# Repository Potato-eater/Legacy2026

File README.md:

# Legacy2026
github repo for Robocup Junior Australia lightweight soccer team

poster for state competition: https://canva.link/pb0ula68jbszzvj

All programs are annotated within their own files.

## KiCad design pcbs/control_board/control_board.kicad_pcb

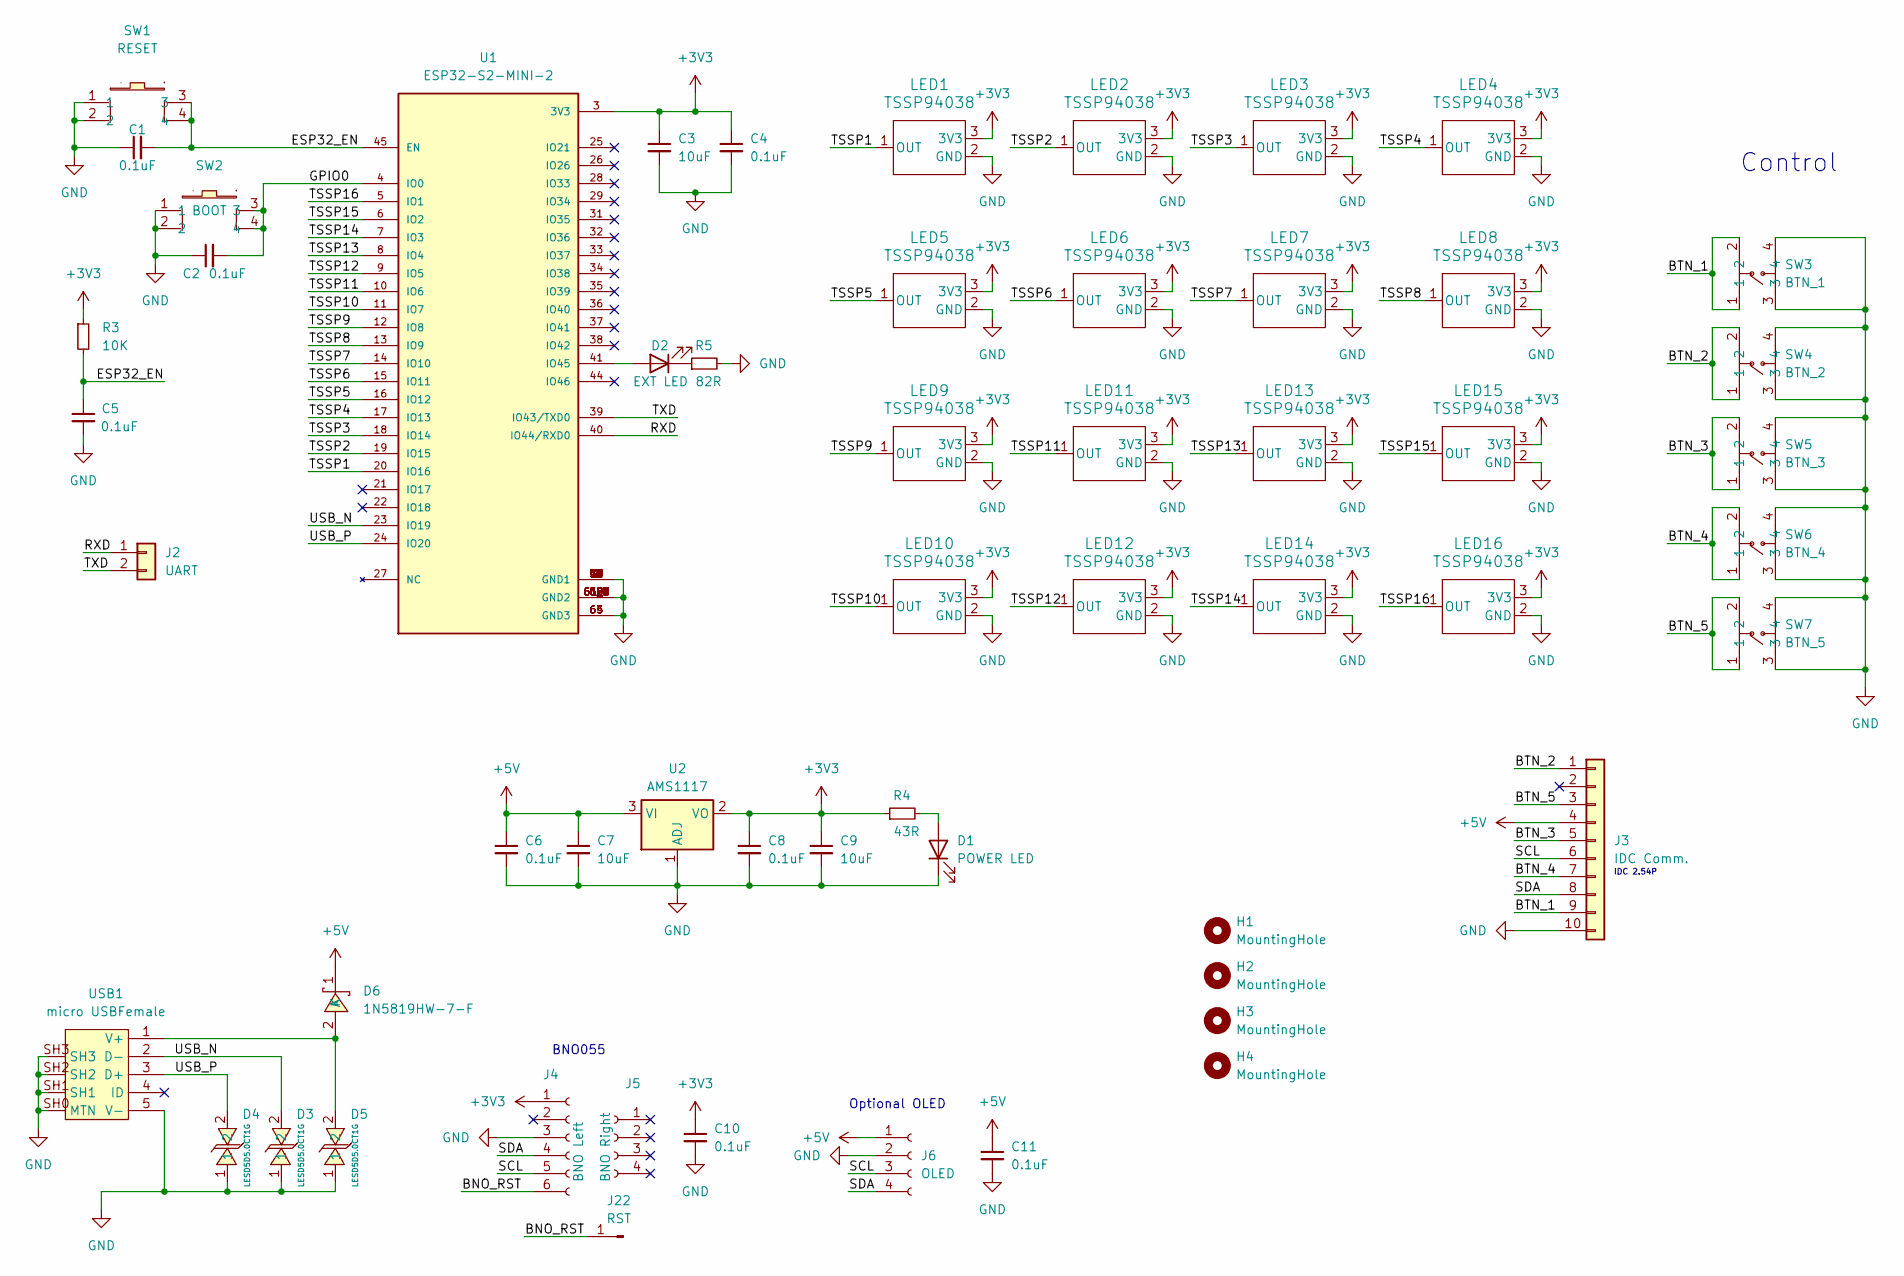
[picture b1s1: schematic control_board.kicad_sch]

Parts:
C1, C2, C4, C5, C6, C8, C10, C11: 0.1uF; C_0402_1005Metric
C3, C7, C9: 10uF; C_0603_1608Metric
D1: POWER LED; LED_0603_1608Metric
D2: EXT LED; LED_0603_1608Metric
D3, D4, D5: LESD5D5.0CT1G; SOD-523_L1.2-W0.8-LS1.6-BI; LCSC Part C5274290
D6: 1N5819HW-7-F; SOD-123_L2.7-W1.6-LS3.7-RD; LCSC Part C82544
H1, H2, H3, H4: MountingHole; MountingHole_3.5mm
J2: UART; JST_XH_B2B-XH-A_1x02_P2.50mm_Vertical
J3: IDC Comm.; IDC-Header_2x05_P2.54mm_Vertical
J4: BNO Left; PinSocket_1x06_P2.54mm_Vertical
J5: BNO Right; PinSocket_1x04_P2.54mm_Vertical
J6: OLED; PinSocket_1x04_P2.54mm_Vertical
J22: RST; PinHeader_1x01_P2.54mm_Vertical
LED1, LED2, LED3, LED4, LED5, LED6, LED7, LED8, LED9, LED10, LED11, LED12, LED13, LED14, LED15, LED16: TSSP94038
R3: 10K; R_0603_1608Metric
R4: 43R; R_0603_1608Metric
R5: 82R; R_0603_1608Metric
SW1: RESET; SW-SMD_4P_PTS810SJM250SMTRLFS; LCSC Part C221897
SW2: BOOT; SW-SMD_4P_PTS810SJM250SMTRLFS; LCSC Part C221897
SW3: BTN_1; SW-TH_4P-L6.0-W6.0-P4.50-LS6.3; LCSC Part C2889001
SW4: BTN_2; SW-TH_4P-L6.0-W6.0-P4.50-LS6.3; LCSC Part C2889001
SW5: BTN_3; SW-TH_4P-L6.0-W6.0-P4.50-LS6.3; LCSC Part C2889001
SW6: BTN_4; SW-TH_4P-L6.0-W6.0-P4.50-LS6.3; LCSC Part C2889001
SW7: BTN_5; SW-TH_4P-L6.0-W6.0-P4.50-LS6.3; LCSC Part C2889001
U1: ESP32-S2-MINI-2; PARTREV v0.5
U2: AMS1117; SOT-223-3_TabPin2
USB1: micro USBFemale; MICRO-USB-SMD_5P-P0.65-H-F_C10418; LCSC Part C10418

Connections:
+3V3: C3.1, C4.1, C8.1, C9.1, C10.1, J4.1, LED1.3 (3V3), LED2.3 (3V3), LED3.3 (3V3), LED4.3 (3V3), LED5.3 (3V3), LED6.3 (3V3), LED7.3 (3V3), LED8.3 (3V3), LED9.3 (3V3), LED10.3 (3V3), LED11.3 (3V3), LED12.3 (3V3), LED13.3 (3V3), LED14.3 (3V3), LED15.3 (3V3), LED16.3 (3V3), R3.1, R4.1, U1.3 (3V3), U2.2 (VO)
+5V: C6.1, C7.1, C11.1, D6.1 (K), J3.4, J6.1, U2.3 (VI)
/BNO_RST: J4.6, J22.1
/BTN_1: J3.9, SW3.1, SW3.2
/BTN_2: J3.1, SW4.1, SW4.2
/BTN_3: J3.5, SW5.1, SW5.2
/BTN_4: J3.7, SW6.1, SW6.2
/BTN_5: J3.3, SW7.1, SW7.2
/ESP32_EN: C1.2, C5.1, R3.2, SW1.3, SW1.4, U1.45 (EN)
/GPIO0: C2.2, SW2.3, SW2.4, U1.4 (IO0)
/RXD: J2.1, U1.40 (IO44/RXD0)
/SCL: J3.6, J4.5, J6.3
/SDA: J3.8, J4.4, J6.4
/TSSP1: LED1.1 (OUT), U1.20 (IO16)
/TSSP2: LED2.1 (OUT), U1.19 (IO15)
/TSSP3: LED3.1 (OUT), U1.18 (IO14)
/TSSP4: LED4.1 (OUT), U1.17 (IO13)
/TSSP5: LED5.1 (OUT), U1.16 (IO12)
/TSSP6: LED6.1 (OUT), U1.15 (IO11)
/TSSP7: LED7.1 (OUT), U1.14 (IO10)
/TSSP8: LED8.1 (OUT), U1.13 (IO9)
/TSSP9: LED9.1 (OUT), U1.12 (IO8)
/TSSP10: LED10.1 (OUT), U1.11 (IO7)
/TSSP11: LED11.1 (OUT), U1.10 (IO6)
/TSSP12: LED12.1 (OUT), U1.9 (IO5)
/TSSP13: LED13.1 (OUT), U1.8 (IO4)
/TSSP14: LED14.1 (OUT), U1.7 (IO3)
/TSSP15: LED15.1 (OUT), U1.6 (IO2)
/TSSP16: LED16.1 (OUT), U1.5 (IO1)
/TXD: J2.2, U1.39 (IO43/TXD0)
/USB_N: D3.2, U1.23 (IO19), USB1.2 (D-)
/USB_P: D4.2, U1.24 (IO20), USB1.3 (D+)
GND: C1.1, C2.1, C3.2, C4.2, C5.2, C6.2, C7.2, C8.2, C9.2, C10.2, C11.2, D1.1 (K), D3.1, D4.1, D5.1, J3.10, J4.3, J6.2, LED1.2 (GND), LED2.2 (GND), LED3.2 (GND), LED4.2 (GND), LED5.2 (GND), LED6.2 (GND), LED7.2 (GND), LED8.2 (GND), LED9.2 (GND), LED10.2 (GND), LED11.2 (GND), LED12.2 (GND), LED13.2 (GND), LED14.2 (GND), LED15.2 (GND), LED16.2 (GND), R5.2, SW1.1, SW1.2, SW2.1, SW2.2, SW3.3, SW3.4, SW4.3, SW4.4, SW5.3, SW5.4, SW6.3, SW6.4, SW7.3, SW7.4, U1.1 (GND1), U1.2 (GND1), U1.30 (GND1), U1.42 (GND1), U1.43 (GND1), U1.46 (GND1), U1.47 (GND1), U1.48 (GND1), U1.49 (GND1), U1.50 (GND1), U1.51 (GND1), U1.52 (GND1), U1.53 (GND1), U1.54 (GND1), U1.55 (GND1), U1.56 (GND2), U1.57 (GND2), U1.58 (GND2), U1.59 (GND2), U1.60 (GND2), U1.61_1 (GND2), U1.61_2 (GND2), U1.61_3 (GND2), U1.61_4 (GND2), U1.61_5 (GND2), U1.61_6 (GND2), U1.61_7 (GND2), U1.61_8 (GND2), U1.61_9 (GND2), U1.62 (GND2), U1.63 (GND3), U1.64 (GND3), U1.65 (GND3), U2.1 (ADJ), USB1.5 (V-), USB1.SH0 (MTN), USB1.SH1, USB1.SH2, USB1.SH3
unnamed: D1.2 (A), R4.2
unnamed: D2.2 (A), U1.41 (IO45)
unnamed: D2.1 (K), R5.1
unnamed: D5.2, D6.2 (A), USB1.1 (V+)

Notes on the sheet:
Optional OLED
Control
BNO055
IDC 2.54P

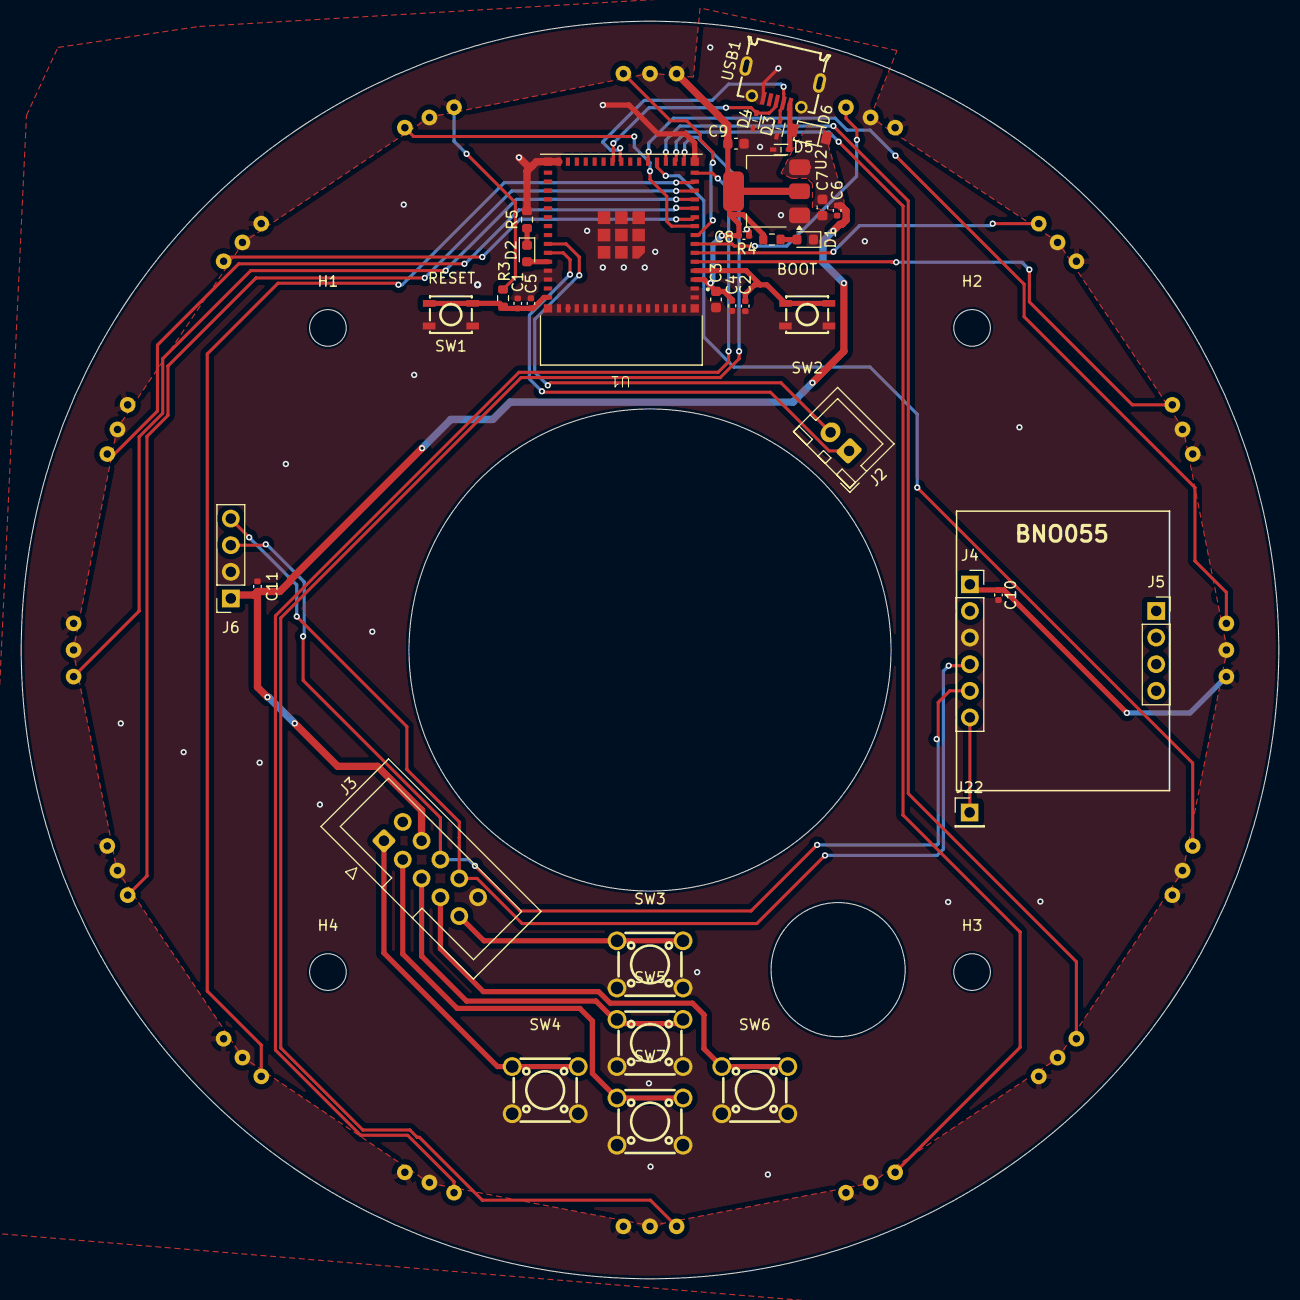
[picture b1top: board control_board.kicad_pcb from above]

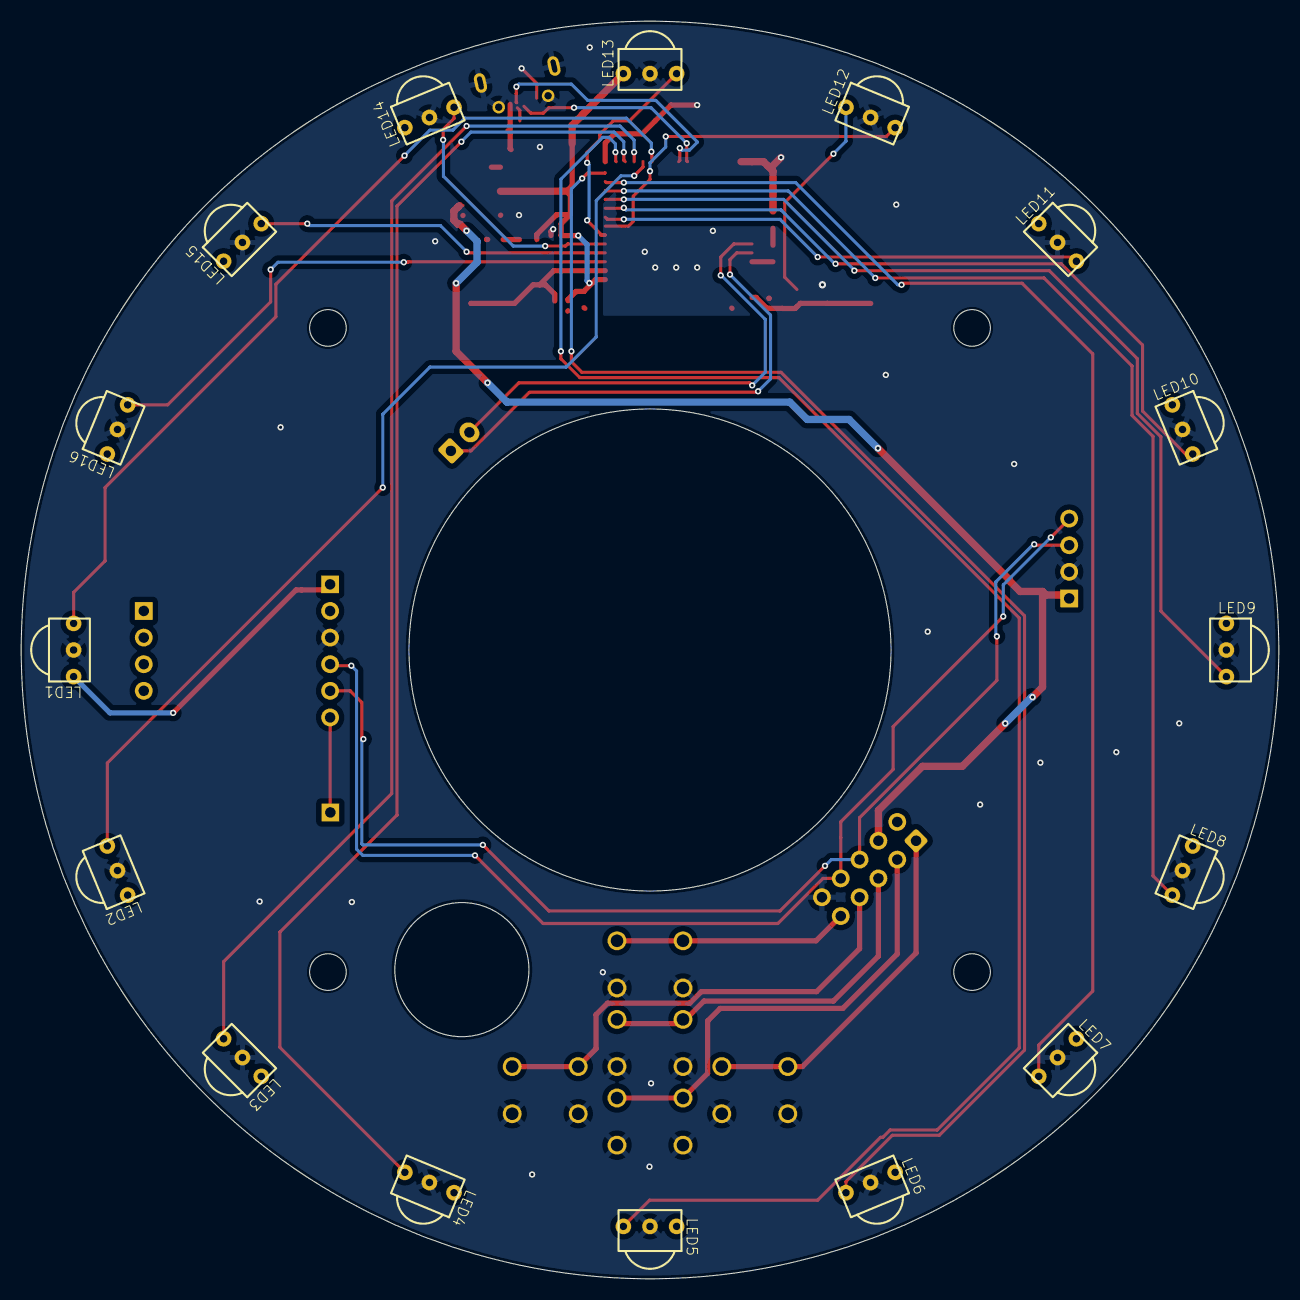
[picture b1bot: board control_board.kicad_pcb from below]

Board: 2 copper layers, 120.0 x 120.0 mm, 56 parts (16 on the bottom side), 37 nets.

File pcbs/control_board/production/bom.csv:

Designator,Footprint,Quantity,Value,LCSC Part #
"C1, C10, C11, C2, C4, C5, C6, C8",0402,8,0.1uF,
"C3, C7, C9",0603,3,10uF,
D1,0603,1,POWER LED,
D2,0603,1,EXT LED,
"D3, D4, D5",SOD-523_L1.2-W0.8-LS1.6-BI,3,LESD5D5.0CT1G,C5274290
D6,SOD-123_L2.7-W1.6-LS3.7-RD,1,1N5819HW-7-F,C82544
J2,JST_XH_B2B-XH-A_1x02_P2.50mm_Vertical,1,UART,
J22,PinHeader_1x01_P2.54mm_Vertical,1,RST,
J3,IDC-Header_2x05_P2.54mm_Vertical,1,IDC Comm.,
J4,PinSocket_1x06_P2.54mm_Vertical,1,BNO Left,
J5,PinSocket_1x04_P2.54mm_Vertical,1,BNO Right,
J6,PinSocket_1x04_P2.54mm_Vertical,1,OLED,
"LED1, LED10, LED11, LED12, LED13, LED14, LED15, LED16, LED2, LED3, LED4, LED5, LED6, LED7, LED8, LED9",TSSP94038,16,TSSP94038,
R3,0603,1,10K,
R4,0603,1,43R,
R5,0603,1,82R,
SW1,SW-SMD_4P_PTS810SJM250SMTRLFS,1,RESET,C221897
SW2,SW-SMD_4P_PTS810SJM250SMTRLFS,1,BOOT,C221897
SW3,SW-TH_4P-L6.0-W6.0-P4.50-LS6.3,1,BTN_1,C2889001
SW4,SW-TH_4P-L6.0-W6.0-P4.50-LS6.3,1,BTN_2,C2889001
SW5,SW-TH_4P-L6.0-W6.0-P4.50-LS6.3,1,BTN_3,C2889001
SW6,SW-TH_4P-L6.0-W6.0-P4.50-LS6.3,1,BTN_4,C2889001
SW7,SW-TH_4P-L6.0-W6.0-P4.50-LS6.3,1,BTN_5,C2889001
U1,ESP32-S2-MINI-2,1,ESP32-S2-MINI-2,
U2,SOT-223-3_TabPin2,1,AMS1117,
USB1,MICRO-USB-SMD_5P-P0.65-H-F_C10418,1,micro USBFemale,C10418

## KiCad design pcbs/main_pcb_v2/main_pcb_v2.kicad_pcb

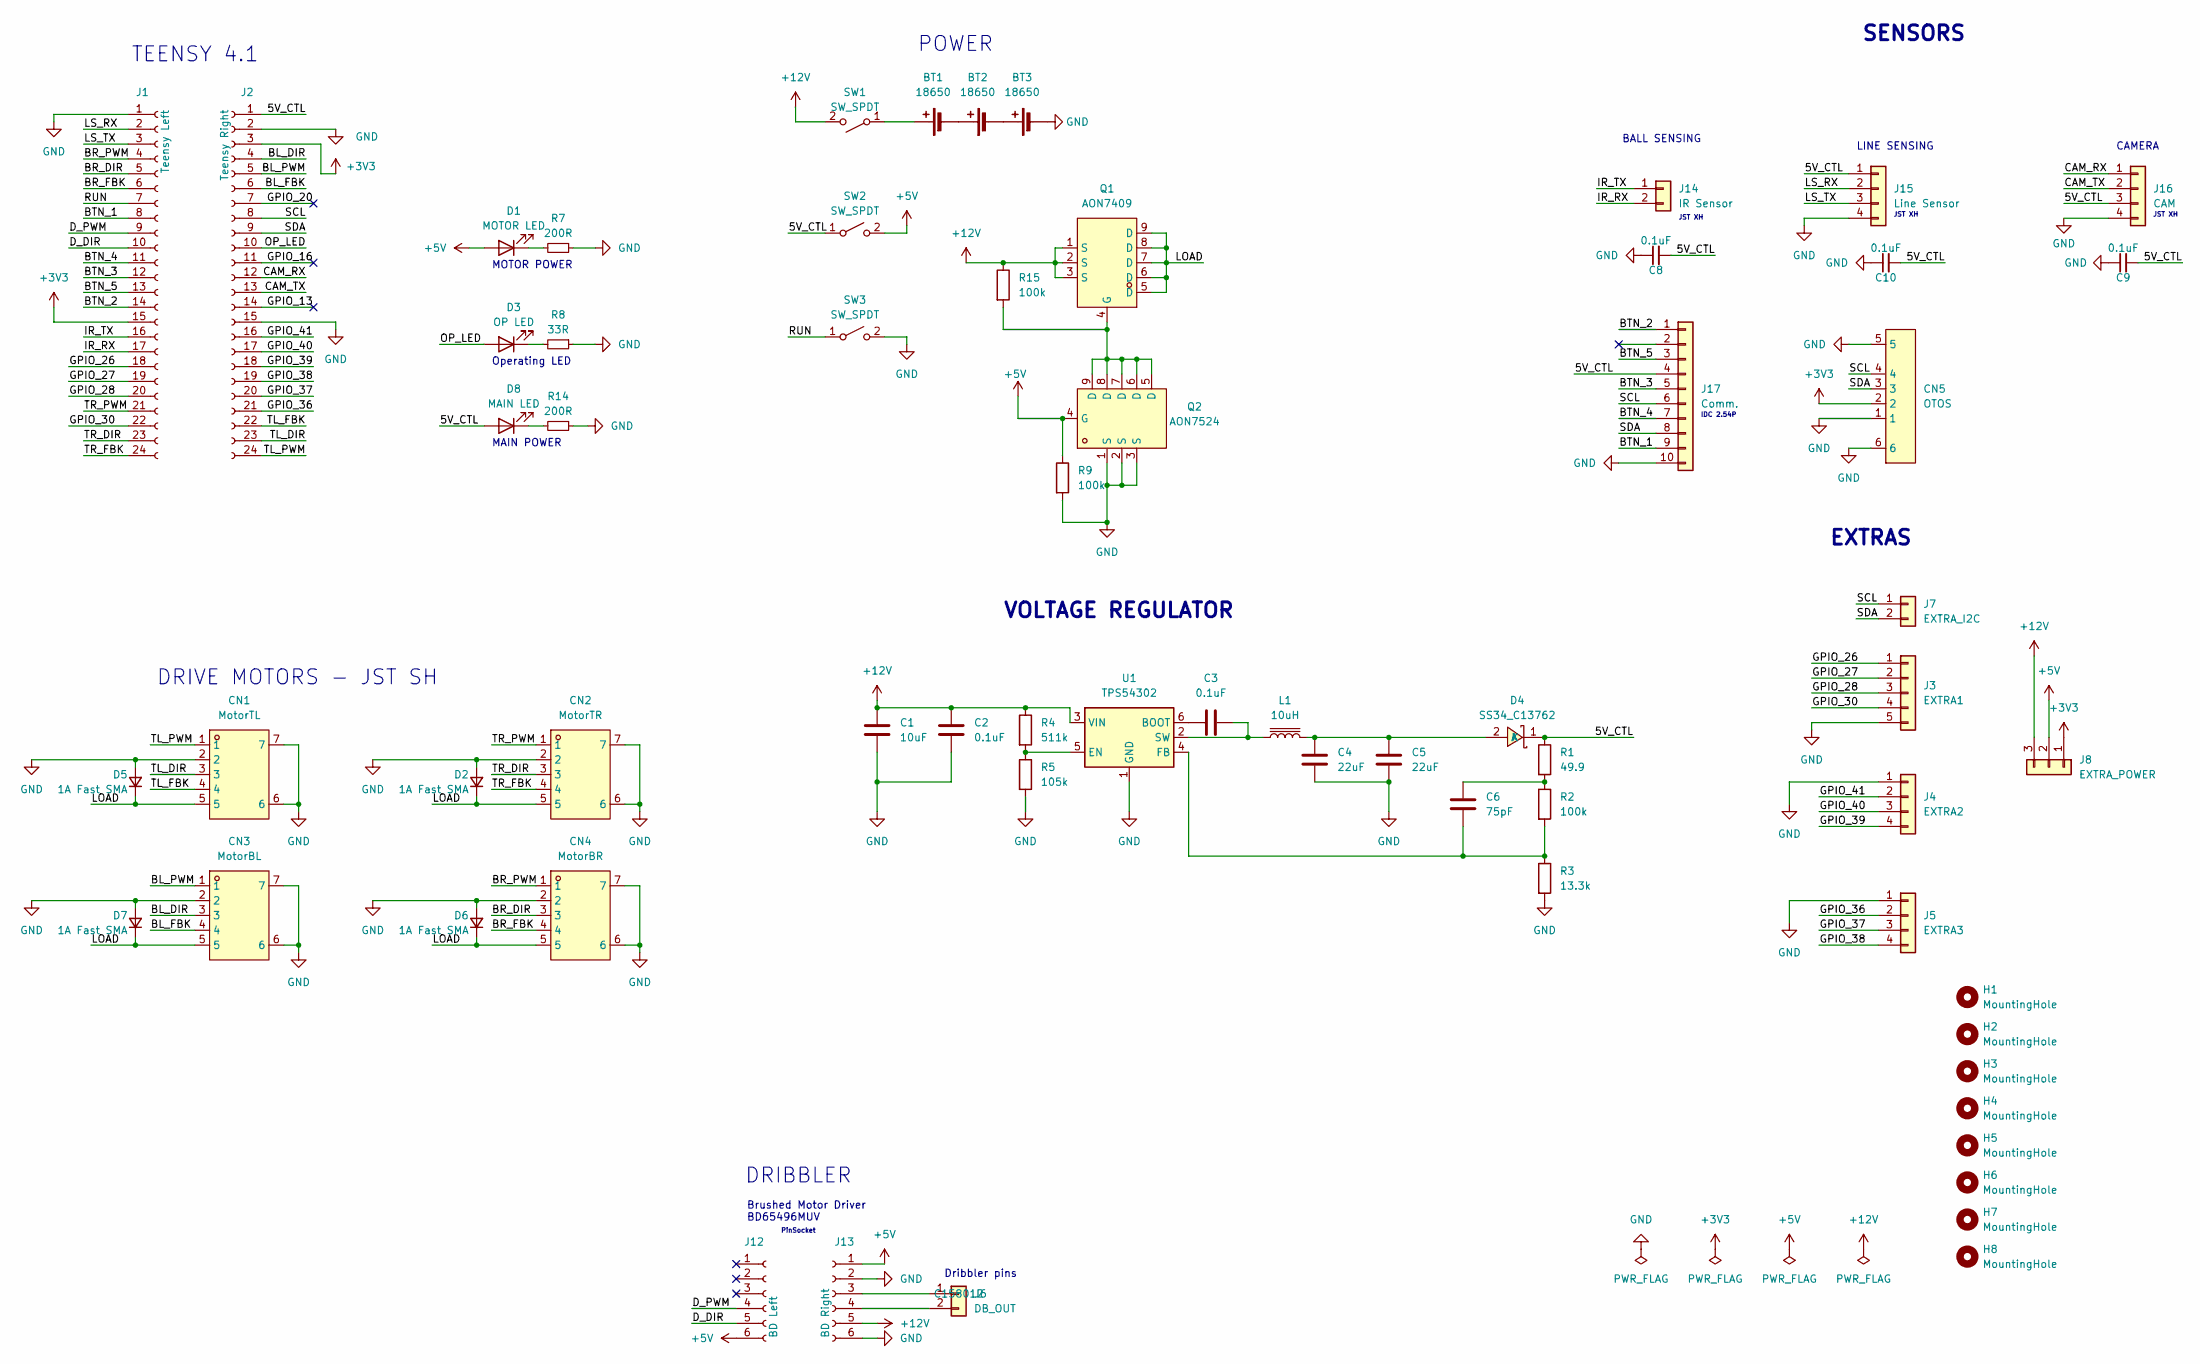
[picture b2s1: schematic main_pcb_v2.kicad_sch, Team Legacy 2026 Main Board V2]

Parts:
BT1, BT2, BT3: 18650; Altronics_S5037
C1: 10uF; C_0805_2012Metric
C2, C3, C8, C9: 0.1uF; C_0805_2012Metric
C4, C5: 22uF; C_0805_2012Metric
C6: 75pF; C_0805_2012Metric
C10: 0.1uF; C_0402_1005Metric
CN1: MotorTL; CONN-SMD_SM05B-SRSS-TB-LF-SN; LCSC Part C136657
CN2: MotorTR; CONN-SMD_SM05B-SRSS-TB-LF-SN; LCSC Part C136657
CN3: MotorBL; CONN-SMD_SM05B-SRSS-TB-LF-SN; LCSC Part C136657
CN4: MotorBR; CONN-SMD_SM05B-SRSS-TB-LF-SN; LCSC Part C136657
CN5: OTOS; CONN-SMD_4P-P1.00_SM04B-SRSS-TB-LF-SN; LCSC Part C160404
D1: MOTOR LED; LED_0603_1608Metric
D2, D5, D6, D7: 1A Fast SMA; D_SMA
D3: OP LED; LED_0805_2012Metric
D4: SS34_C13762; SMB_L4.6-W3.6-LS5.3-RD; LCSC Part C13762
D8: MAIN LED; LED_0603_1608Metric
H1, H2, H3, H4, H5, H6, H7, H8: MountingHole; MountingHole_3.5mm
J1: Teensy Left; PinSocket_1x24_P2.54mm_Vertical
J2: Teensy Right; PinSocket_1x24_P2.54mm_Vertical
J3: EXTRA1; PinSocket_1x05_P2.54mm_Vertical
J4: EXTRA2; PinSocket_1x04_P2.54mm_Vertical
J5: EXTRA3; PinSocket_1x04_P2.54mm_Vertical
J6: DB_OUT; JST_XH_B2B-XH-A_1x02_P2.50mm_Vertical
J7: EXTRA_I2C; JST_XH_B2B-XH-A_1x02_P2.50mm_Vertical
J8: EXTRA_POWER; PinSocket_1x03_P2.54mm_Vertical
J12: BD Left; PinSocket_1x06_P2.54mm_Vertical
J13: BD Right; PinSocket_1x06_P2.54mm_Vertical
J14: IR Sensor; JST_XH_B2B-XH-A_1x02_P2.50mm_Vertical
J15: Line Sensor; JST_XH_B4B-XH-A_1x04_P2.50mm_Vertical
J16: CAM; JST_XH_B4B-XH-A_1x04_P2.50mm_Vertical
J17: Comm.; IDC-Header_2x05_P2.54mm_Vertical
L1: 10uH; IND-SMD_L11.0-W10.0
Q1: AON7409; WDFN-8_L3.0-W3.0-P0.65-LS3.3-BL-EP; MPN AON7409; LCSC Part C41348138
Q2: AON7524; DFN-8_L3.0-W3.0-P0.65-BL; LCSC Part C431195
R1: 49.9; R_0603_1608Metric
R2, R9, R15: 100k; R_0603_1608Metric
R3: 13.3k; R_0603_1608Metric
R4: 511k; R_0603_1608Metric
R5: 105k; R_0603_1608Metric
R7, R14: 200R; R_0603_1608Metric
R8: 33R; R_0603_1608Metric
SW1, SW2, SW3: SW_SPDT; CONN-TH_2P-P5.00_WJ128V-5.0-2P
U1: TPS54302; SOT-23-6

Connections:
+3V3: CN5.2, J1.15, J2.3, J8.1
+5V: D1.2 (A), J8.2, J12.6, J13.1, Q2.4 (G), R9.1, SW2.2 (B)
+12V: C1.1, C2.1, J8.3, J13.5, Q1.1 (S), Q1.2 (S), Q1.3 (S), R4.1, R15.1, SW1.2 (B), U1.3 (VIN)
/5V_CTL: C8.2, C9.2, C10.2, D4.1 (K), D8.2 (A), J2.1, J15.1, J16.3, J17.4, R1.1, SW2.1 (A)
/BL_DIR: CN3.3, J2.4
/BL_FBK: CN3.4, J2.6
/BL_PWM: CN3.1, J2.5
/BR_DIR: CN4.3, J1.5
/BR_FBK: CN4.4, J1.6
/BR_PWM: CN4.1, J1.4
/BTN_1: J1.8, J17.9
/BTN_2: J1.14, J17.1
/BTN_3: J1.12, J17.5
/BTN_4: J1.11, J17.7
/BTN_5: J1.13, J17.3
/CAM_RX: J2.12, J16.1
/CAM_TX: J2.13, J16.2
/D_DIR: J1.10, J12.5
/D_PWM: J1.9, J12.4
/GPIO_13: J2.14
/GPIO_16: J2.11
/GPIO_20: J2.7
/GPIO_26: J1.18, J3.1
/GPIO_27: J1.19, J3.2
/GPIO_28: J1.20, J3.3
/GPIO_30: J1.22, J3.4
/GPIO_36: J2.21, J5.2
/GPIO_37: J2.20, J5.3
/GPIO_38: J2.19, J5.4
/GPIO_39: J2.18, J4.4
/GPIO_40: J2.17, J4.3
/GPIO_41: J2.16, J4.2
/IR_RX: J1.17, J14.2
/IR_TX: J1.16, J14.1
/LOAD: CN1.5, CN2.5, CN3.5, CN4.5, D2.1 (K), D5.1 (K), D6.1 (K), D7.1 (K), Q1.5 (D), Q1.6 (D), Q1.7 (D), Q1.8 (D), Q1.9 (D)
/LS_RX: J1.2, J15.2
/LS_TX: J1.3, J15.3
/OP_LED: D3.2 (A), J2.10
/RUN: J1.7, SW3.1 (A)
/SCL: CN5.4, J2.8, J7.1, J17.6
/SDA: CN5.3, J2.9, J7.2, J17.8
/TL_DIR: CN1.3, J2.23
/TL_FBK: CN1.4, J2.22
/TL_PWM: CN1.1, J2.24
/TR_DIR: CN2.3, J1.23
/TR_FBK: CN2.4, J1.24
/TR_PWM: CN2.1, J1.21
GND: BT3.2 (-), C1.2, C2.2, C4.1, C5.1, C8.1, C9.1, C10.1, CN1.2, CN1.6, CN1.7, CN2.2, CN2.6, CN2.7, CN3.2, CN3.6, CN3.7, CN4.2, CN4.6, CN4.7, CN5.1, CN5.5, CN5.6, D2.2 (A), D5.2 (A), D6.2 (A), D7.2 (A), J1.1, J2.2, J2.15, J3.5, J4.1, J5.1, J13.2, J13.6, J15.4, J16.4, J17.10, Q2.1 (S), Q2.2 (S), Q2.3 (S), R3.2, R5.2, R7.1, R8.1, R9.2, R14.1, SW3.2 (B), U1.1 (GND)
unnamed: BT1.1 (+), SW1.1 (A)
unnamed: BT1.2 (-), BT2.1 (+)
unnamed: BT2.2 (-), BT3.1 (+)
unnamed: C6.2, R1.2, R2.1
unnamed: D1.1 (K), R7.2
unnamed: D3.1 (K), R8.2
unnamed: C4.2, C5.2, D4.2 (A), L1.2
unnamed: D8.1 (K), R14.2
unnamed: J6.1, J13.3
unnamed: J6.2, J13.4
unnamed: Q1.4 (G), Q2.5 (D), Q2.6 (D), Q2.7 (D), Q2.8 (D), Q2.9 (D), R15.2
unnamed: C3.1, U1.6 (BOOT)
unnamed: R4.2, R5.1, U1.5 (EN)
unnamed: C6.1, R2.2, R3.1, U1.4 (FB)
unnamed: C3.2, L1.1, U1.2 (SW)

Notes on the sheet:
PinSocket
JST XH
CAMERA
MAIN POWER
BALL SENSING
Dribbler pins
DRIBBLER
VOLTAGE REGULATOR
DRIVE MOTORS - JST SH
SENSORS
Operating LED
LINE SENSING
IDC 2.54P
Brushed Motor Driver BD65496MUV
EXTRAS
TEENSY 4.1
POWER
MOTOR POWER

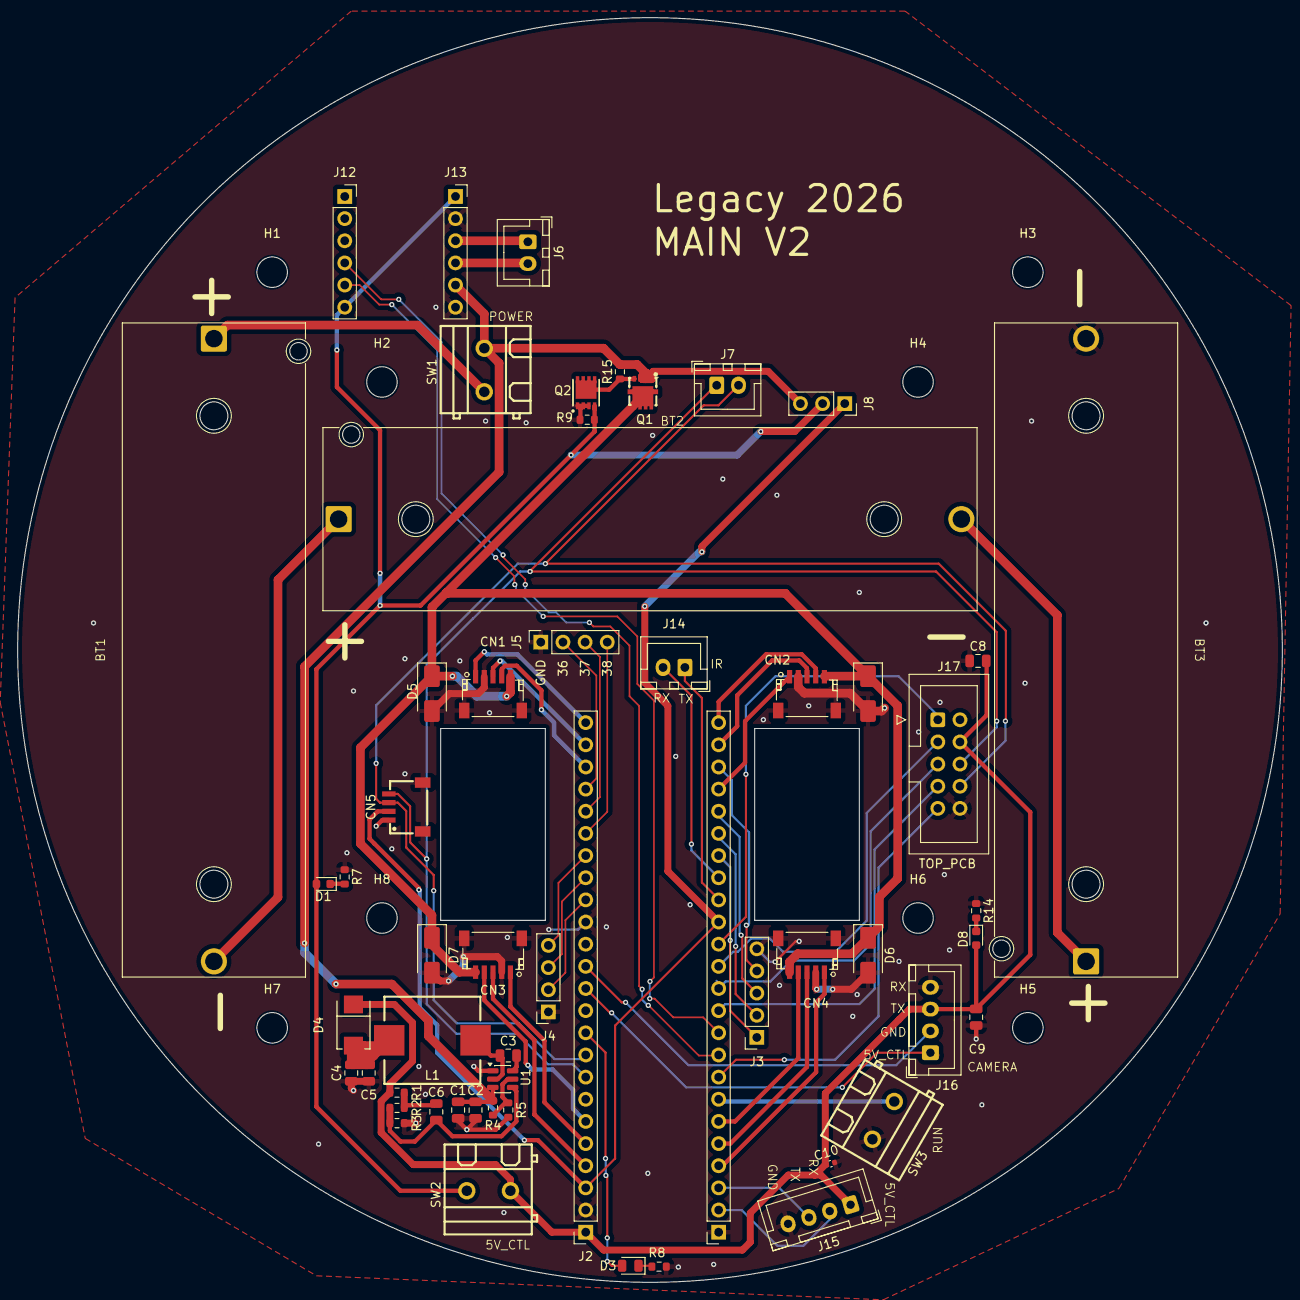
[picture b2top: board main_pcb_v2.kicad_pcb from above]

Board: 2 copper layers, 145.0 x 145.0 mm, 64 parts (0 on the bottom side), 60 nets.

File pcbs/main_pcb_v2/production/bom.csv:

Designator,Footprint,Quantity,Value,LCSC Part #
"BT1, BT2, BT3",Altronics_S5037,3,18650,
C1,0805,1,10uF,
C10,0402,1,0.1uF,
"C2, C3, C8, C9",0805,4,0.1uF,
"C4, C5",0805,2,22uF,
C6,0805,1,75pF,
CN1,CONN-SMD_SM05B-SRSS-TB-LF-SN,1,MotorTL,C136657
CN2,CONN-SMD_SM05B-SRSS-TB-LF-SN,1,MotorTR,C136657
CN3,CONN-SMD_SM05B-SRSS-TB-LF-SN,1,MotorBL,C136657
CN4,CONN-SMD_SM05B-SRSS-TB-LF-SN,1,MotorBR,C136657
CN5,CONN-SMD_4P-P1.00_SM04B-SRSS-TB-LF-SN,1,OTOS,C160404
D1,0603,1,MOTOR LED,
"D2, D5, D6, D7",D_SMA,4,1A Fast SMA,
D3,0805,1,OP LED,
D4,SMB_L4.6-W3.6-LS5.3-RD,1,SS34_C13762,C13762
D8,0603,1,MAIN LED,
J1,PinSocket_1x24_P2.54mm_Vertical,1,Teensy Left,
J12,PinSocket_1x06_P2.54mm_Vertical,1,BD Left,
J13,PinSocket_1x06_P2.54mm_Vertical,1,BD Right,
J14,JST_XH_B2B-XH-A_1x02_P2.50mm_Vertical,1,IR Sensor,
J15,JST_XH_B4B-XH-A_1x04_P2.50mm_Vertical,1,Line Sensor,
J16,JST_XH_B4B-XH-A_1x04_P2.50mm_Vertical,1,CAM,
J17,IDC-Header_2x05_P2.54mm_Vertical,1,Comm.,
J2,PinSocket_1x24_P2.54mm_Vertical,1,Teensy Right,
J3,PinSocket_1x05_P2.54mm_Vertical,1,EXTRA1,
J4,PinSocket_1x04_P2.54mm_Vertical,1,EXTRA2,
J5,PinSocket_1x04_P2.54mm_Vertical,1,EXTRA3,
J6,JST_XH_B2B-XH-A_1x02_P2.50mm_Vertical,1,DB_OUT,
J7,JST_XH_B2B-XH-A_1x02_P2.50mm_Vertical,1,EXTRA_I2C,
J8,PinSocket_1x03_P2.54mm_Vertical,1,Conn_01x03,
L1,IND-SMD_L11.0-W10.0,1,10uH,
Q1,WDFN-8_L3.0-W3.0-P0.65-LS3.3-BL-EP,1,AON7409,C41348138
Q2,DFN-8_L3.0-W3.0-P0.65-BL,1,AON7524,C431195
R1,0603,1,49.9,
"R14, R7",0603,2,200R,
"R15, R2, R9",0603,3,100k,
R3,0603,1,13.3k,
R4,0603,1,511k,
R5,0603,1,105k,
R8,0603,1,33R,
"SW1, SW2, SW3",CONN-TH_2P-P5.00_WJ128V-5.0-2P,3,SW_SPDT,
U1,SOT-23-6,1,TPS54302,

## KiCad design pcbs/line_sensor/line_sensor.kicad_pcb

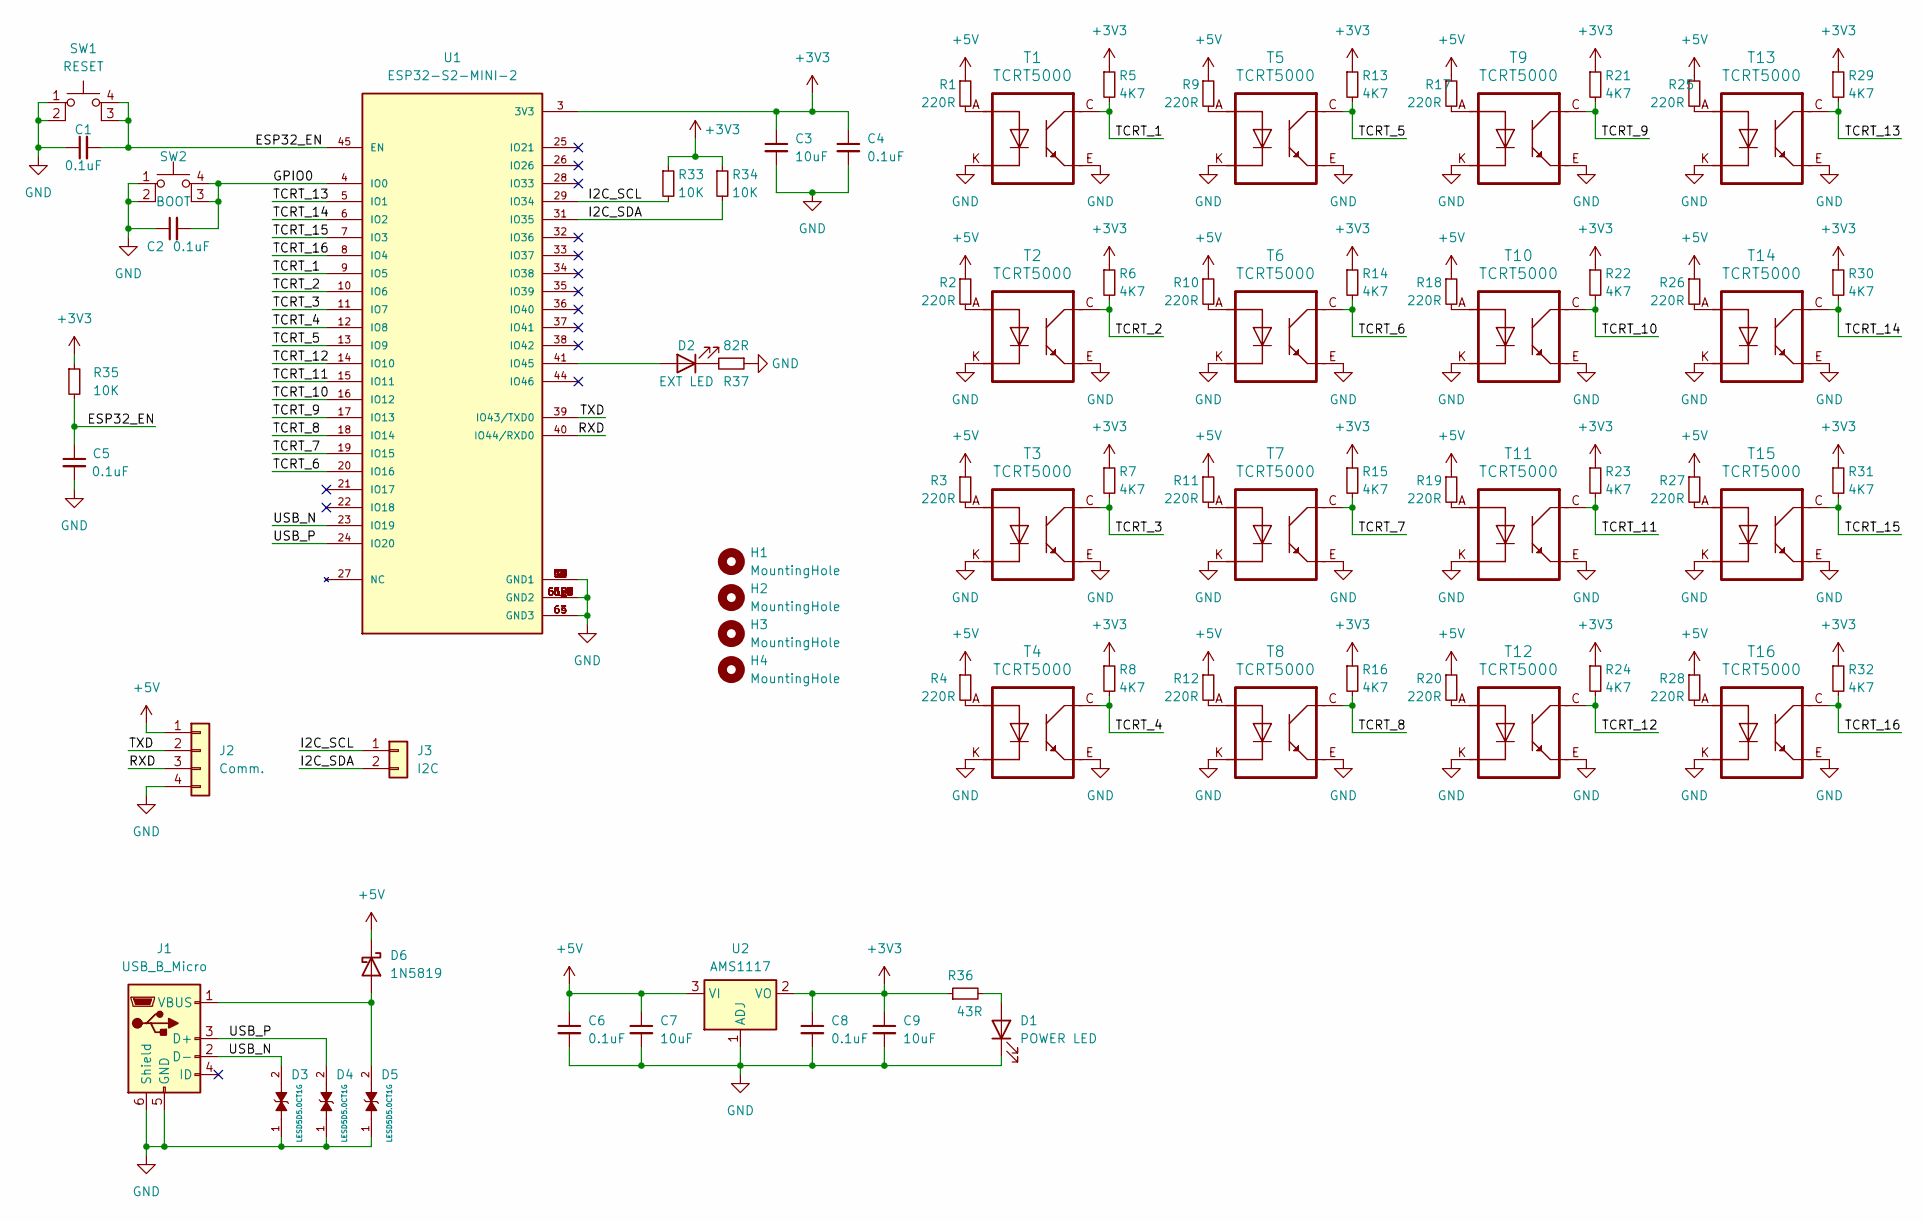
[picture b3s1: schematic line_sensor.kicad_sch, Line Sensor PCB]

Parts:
C1, C2, C4, C5, C6, C8: 0.1uF; C_0402_1005Metric
C3, C7, C9: 10uF; C_0603_1608Metric
D1: POWER LED; LED_0603_1608Metric
D2: EXT LED; LED_0603_1608Metric
D3, D4, D5: LESD5D5.0CT1G; TVS_LESD5D5.0CT1G; PARTREV O
D6: 1N5819; D_SOD-123
H1, H2, H3, H4: MountingHole; MountingHole_3.2mm_M3_Pad
J1: USB_B_Micro; C10418
J2: Comm.; JST_XH_B4B-XH-A_1x04_P2.50mm_Vertical
J3: I2C; JST_XH_B2B-XH-A_1x02_P2.50mm_Vertical
R1, R2, R3, R4, R9, R10, R11, R12, R17, R18, R19, R20, R25, R26, R27, R28: 220R; R_0603_1608Metric
R5, R6, R7, R8, R13, R14, R15, R16, R21, R22, R23, R24, R29, R30, R31, R32: 4K7; R_0603_1608Metric
R33, R34, R35: 10K; R_0603_1608Metric
R36: 43R; R_0603_1608Metric
R37: 82R; C_0603_1608Metric
SW1: RESET; SW_SPST_PTS810
SW2: BOOT; SW_SPST_PTS810
T1, T2, T3, T4, T5, T6, T7, T8, T9, T10, T11, T12, T13, T14, T15, T16: TCRT5000
U1: ESP32-S2-MINI-2; XCVR_ESP32-S2-MINI-2; PARTREV v0.5
U2: AMS1117; SOT-223-3_TabPin2

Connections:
+3V3: C3.1, C4.1, C8.1, C9.1, R5.1, R6.1, R7.1, R8.1, R13.1, R14.1, R15.1, R16.1, R21.1, R22.1, R23.1, R24.1, R29.1, R30.1, R31.1, R32.1, R33.1, R34.1, R35.1, R36.1, U1.3 (3V3), U2.2 (VO)
+5V: C6.1, C7.1, D6.1 (K), J2.1, R1.1, R2.1, R3.1, R4.1, R9.1, R10.1, R11.1, R12.1, R17.1, R18.1, R19.1, R20.1, R25.1, R26.1, R27.1, R28.1, U2.3 (VI)
/ESP32_EN: C1.2, C5.1, R35.2, SW1.3 (K), SW1.4 (A), U1.45 (EN)
/GPIO0: C2.2, SW2.3 (K), SW2.4 (A), U1.4 (IO0)
/I2C_SCL: J3.1, R33.2, U1.29 (IO34)
/I2C_SDA: J3.2, R34.2, U1.31 (IO35)
/RXD: J2.3, U1.40 (IO44/RXD0)
/TCRT_1: R5.2, T1.C (Collector), U1.9 (IO5)
/TCRT_2: R6.2, T2.C (Collector), U1.10 (IO6)
/TCRT_3: R7.2, T3.C (Collector), U1.11 (IO7)
/TCRT_4: R8.2, T4.C (Collector), U1.12 (IO8)
/TCRT_5: R13.2, T5.C (Collector), U1.13 (IO9)
/TCRT_6: R14.2, T6.C (Collector), U1.20 (IO16)
/TCRT_7: R15.2, T7.C (Collector), U1.19 (IO15)
/TCRT_8: R16.2, T8.C (Collector), U1.18 (IO14)
/TCRT_9: R21.2, T9.C (Collector), U1.17 (IO13)
/TCRT_10: R22.2, T10.C (Collector), U1.16 (IO12)
/TCRT_11: R23.2, T11.C (Collector), U1.15 (IO11)
/TCRT_12: R24.2, T12.C (Collector), U1.14 (IO10)
/TCRT_13: R29.2, T13.C (Collector), U1.5 (IO1)
/TCRT_14: R30.2, T14.C (Collector), U1.6 (IO2)
/TCRT_15: R31.2, T15.C (Collector), U1.7 (IO3)
/TCRT_16: R32.2, T16.C (Collector), U1.8 (IO4)
/TXD: J2.2, U1.39 (IO43/TXD0)
/USB_N: D3.2, J1.2 (D-), U1.23 (IO19)
/USB_P: D4.2, J1.3 (D+), U1.24 (IO20)
GND: C1.1, C2.1, C3.2, C4.2, C5.2, C6.2, C7.2, C8.2, C9.2, D1.1 (K), D3.1, D4.1, D5.1, J1.5 (GND), J1.6 (Shield), J2.4, R37.1, SW1.1, SW1.2, SW2.1, SW2.2, T1.E (Emitter), T1.K (Cathode), T2.E (Emitter), T2.K (Cathode), T3.E (Emitter), T3.K (Cathode), T4.E (Emitter), T4.K (Cathode), T5.E (Emitter), T5.K (Cathode), T6.E (Emitter), T6.K (Cathode), T7.E (Emitter), T7.K (Cathode), T8.E (Emitter), T8.K (Cathode), T9.E (Emitter), T9.K (Cathode), T10.E (Emitter), T10.K (Cathode), T11.E (Emitter), T11.K (Cathode), T12.E (Emitter), T12.K (Cathode), T13.E (Emitter), T13.K (Cathode), T14.E (Emitter), T14.K (Cathode), T15.E (Emitter), T15.K (Cathode), T16.E (Emitter), T16.K (Cathode), U1.1 (GND1), U1.2 (GND1), U1.30 (GND1), U1.42 (GND1), U1.43 (GND1), U1.46 (GND1), U1.47 (GND1), U1.48 (GND1), U1.49 (GND1), U1.50 (GND1), U1.51 (GND1), U1.52 (GND1), U1.53 (GND1), U1.54 (GND1), U1.55 (GND1), U1.56 (GND2), U1.57 (GND2), U1.58 (GND2), U1.59 (GND2), U1.60 (GND2), U1.61_1 (GND2), U1.61_2 (GND2), U1.61_3 (GND2), U1.61_4 (GND2), U1.61_5 (GND2), U1.61_6 (GND2), U1.61_7 (GND2), U1.61_8 (GND2), U1.61_9 (GND2), U1.62 (GND2), U1.63 (GND3), U1.64 (GND3), U1.65 (GND3), U2.1 (ADJ)
unnamed: D1.2 (A), R36.2
unnamed: D2.2 (A), U1.41 (IO45)
unnamed: D2.1 (K), R37.2
unnamed: D5.2, D6.2 (A), J1.1 (VBUS)
unnamed: R1.2, T1.A (Anode)
unnamed: R2.2, T2.A (Anode)
unnamed: R3.2, T3.A (Anode)
unnamed: R4.2, T4.A (Anode)
unnamed: R9.2, T5.A (Anode)
unnamed: R10.2, T6.A (Anode)
unnamed: R11.2, T7.A (Anode)
unnamed: R12.2, T8.A (Anode)
unnamed: R17.2, T9.A (Anode)
unnamed: R18.2, T10.A (Anode)
unnamed: R19.2, T11.A (Anode)
unnamed: R20.2, T12.A (Anode)
unnamed: R25.2, T13.A (Anode)
unnamed: R26.2, T14.A (Anode)
unnamed: R27.2, T15.A (Anode)
unnamed: R28.2, T16.A (Anode)
